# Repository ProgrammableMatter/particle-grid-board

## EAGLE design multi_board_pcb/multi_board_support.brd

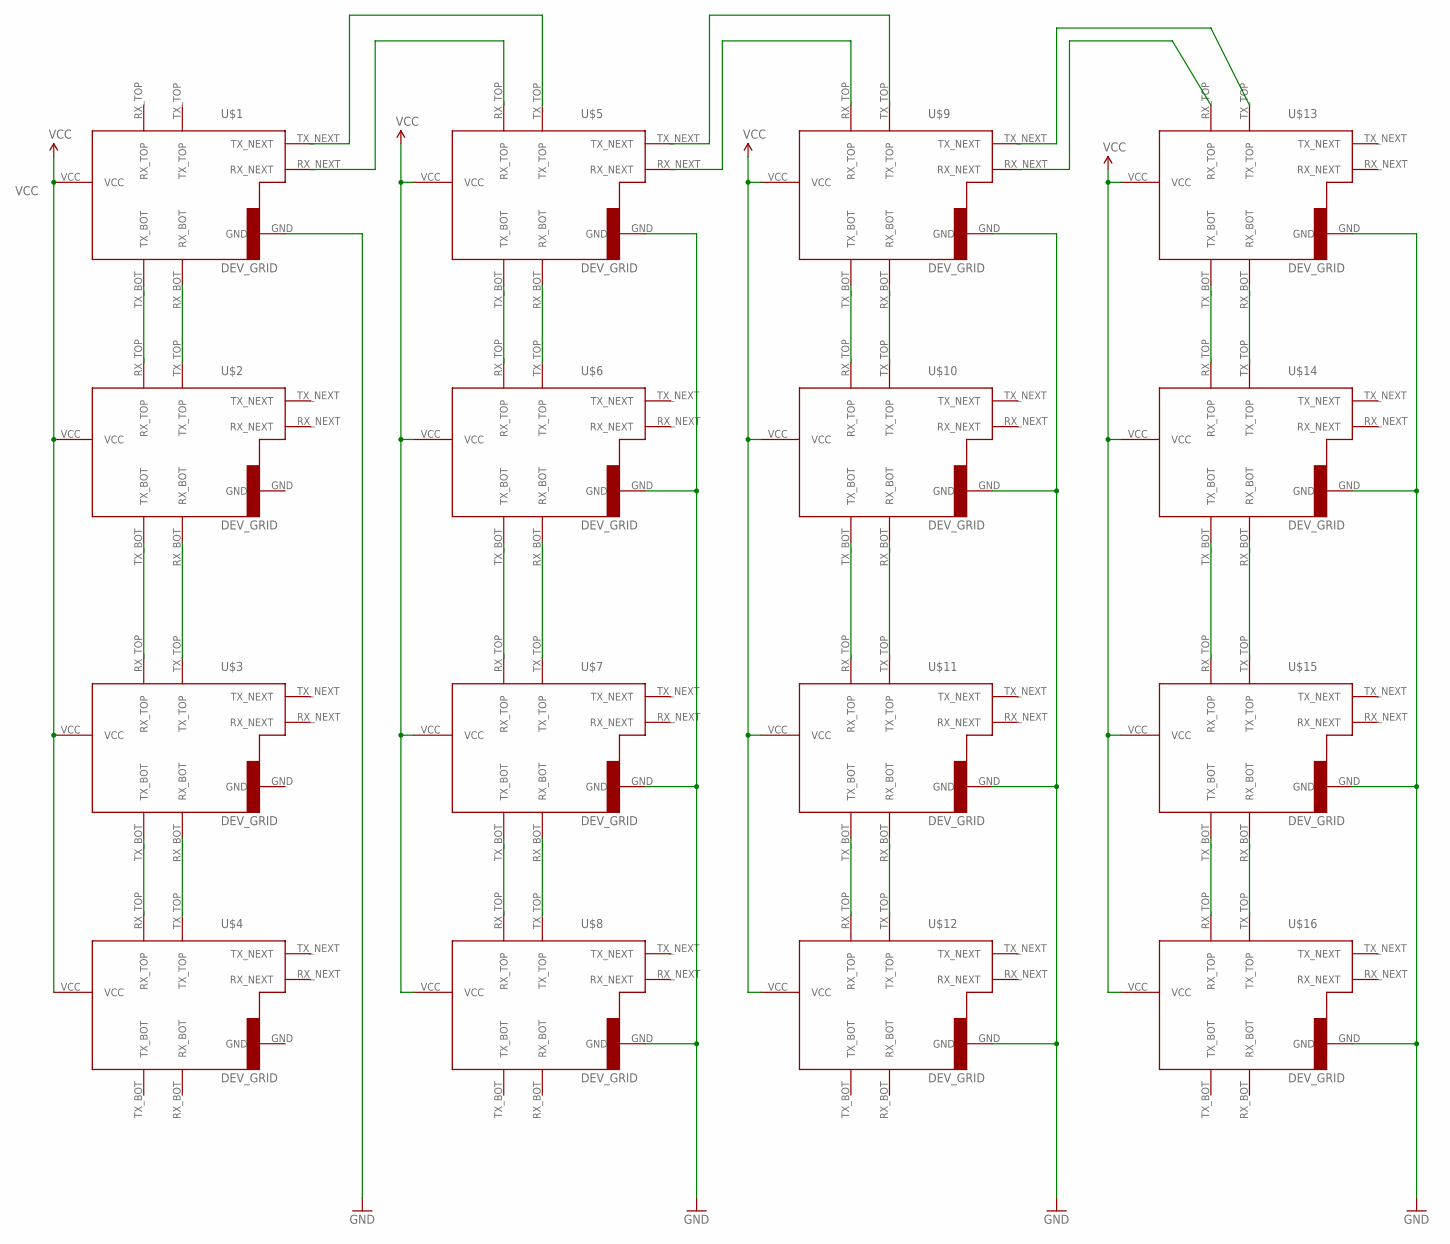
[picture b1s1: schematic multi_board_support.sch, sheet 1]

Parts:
U$1, U$2, U$3, U$4, U$5, U$6, U$7, U$8, U$9, U$10, U$11, U$12, U$13, U$14, U$15, U$16: DEV_GRID; PCB_LAY

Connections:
GND: U$1.GND, U$2.GND, U$3.GND, U$4.GND, U$5.GND, U$6.GND, U$7.GND, U$8.GND, U$9.GND, U$10.GND, U$11.GND, U$12.GND, U$13.GND, U$14.GND, U$15.GND, U$16.GND
unnamed: U$1.TX_BOT, U$2.RX_TOP
unnamed: U$1.RX_BOT, U$2.TX_TOP
unnamed: U$2.TX_BOT, U$3.RX_TOP
unnamed: U$2.RX_BOT, U$3.TX_TOP
unnamed: U$3.TX_BOT, U$4.RX_TOP
unnamed: U$3.RX_BOT, U$4.TX_TOP
unnamed: U$5.TX_BOT, U$6.RX_TOP
unnamed: U$5.RX_BOT, U$6.TX_TOP
unnamed: U$6.TX_BOT, U$7.RX_TOP
unnamed: U$6.RX_BOT, U$7.TX_TOP
unnamed: U$7.TX_BOT, U$8.RX_TOP
unnamed: U$7.RX_BOT, U$8.TX_TOP
unnamed: U$9.TX_BOT, U$10.RX_TOP
unnamed: U$9.RX_BOT, U$10.TX_TOP
unnamed: U$10.TX_BOT, U$11.RX_TOP
unnamed: U$10.RX_BOT, U$11.TX_TOP
unnamed: U$11.TX_BOT, U$12.RX_TOP
unnamed: U$11.RX_BOT, U$12.TX_TOP
unnamed: U$13.TX_BOT, U$14.RX_TOP
unnamed: U$13.RX_BOT, U$14.TX_TOP
unnamed: U$14.TX_BOT, U$15.RX_TOP
unnamed: U$14.RX_BOT, U$15.TX_TOP
unnamed: U$15.TX_BOT, U$16.RX_TOP
unnamed: U$15.RX_BOT, U$16.TX_TOP
unnamed: U$1.TX_NEXT, U$5.TX_TOP
unnamed: U$1.RX_NEXT, U$5.RX_TOP
unnamed: U$5.TX_NEXT, U$9.TX_TOP
unnamed: U$5.RX_NEXT, U$9.RX_TOP
unnamed: U$9.TX_NEXT, U$13.TX_TOP
unnamed: U$9.RX_NEXT, U$13.RX_TOP
VCC: U$1.VCC, U$2.VCC, U$3.VCC, U$4.VCC, U$5.VCC, U$6.VCC, U$7.VCC, U$8.VCC, U$9.VCC, U$10.VCC, U$11.VCC, U$12.VCC, U$13.VCC, U$14.VCC, U$15.VCC, U$16.VCC

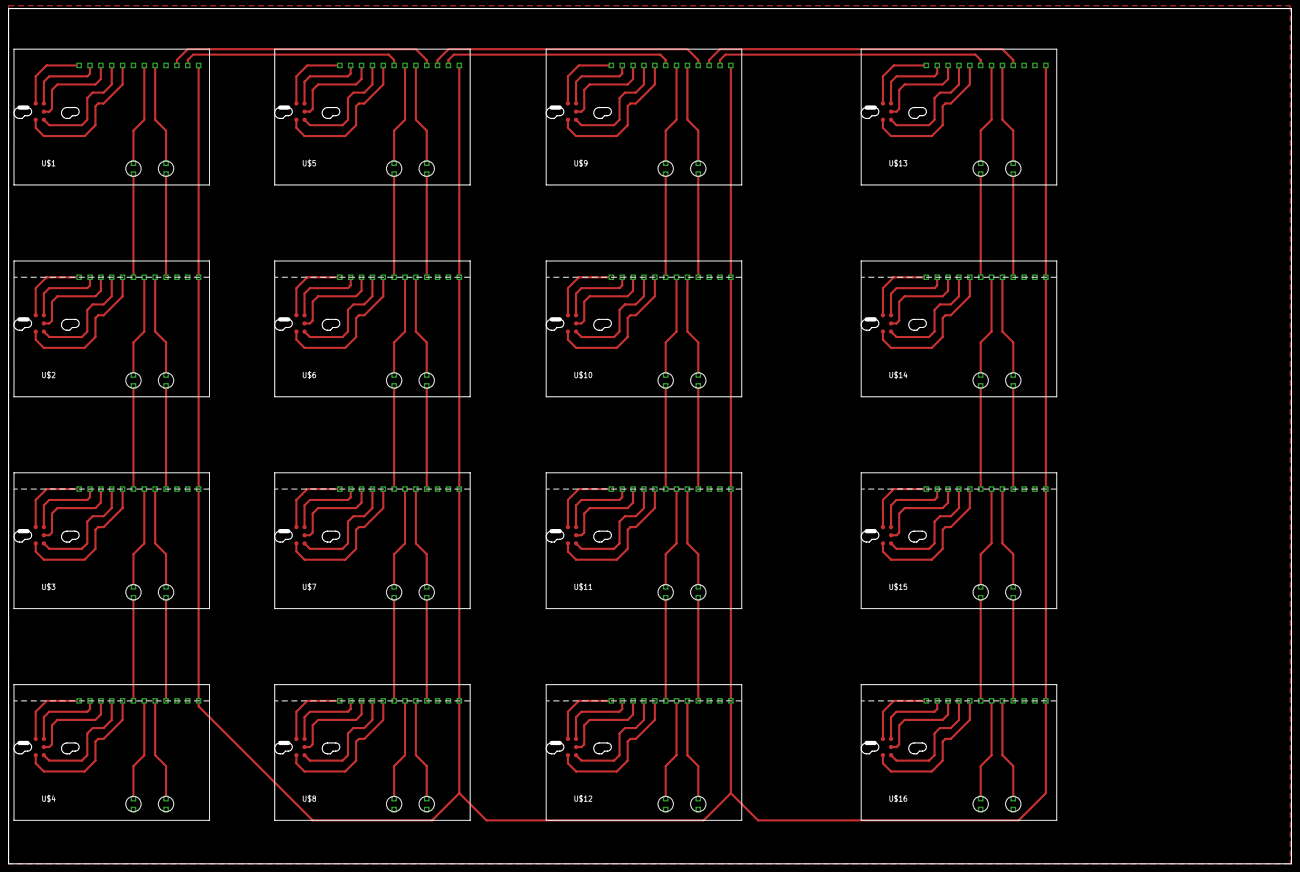
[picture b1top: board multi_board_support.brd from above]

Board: 2 copper layers, 300.0 x 200.0 mm, 16 parts (0 on the bottom side), 32 nets.

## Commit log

2016-02-03 initial import

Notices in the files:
parts and their libraries:
SparkFun: Licensing: CC v3.0 Share-Alike You are welcome to use this library for commercial purposes.
